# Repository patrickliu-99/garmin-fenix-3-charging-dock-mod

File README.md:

# garmin-fenix-3-charging-dock-mod
A quick PCB to add USB C charging to the Garmin Fenix 3 charging dock. Project made in KiCad 5.

# About
One of the charging clips I had for my Fenix 3 HR started failing - looked like the cable was damaged from overuse. I saw on Amazon that
replacements were available using USB micro B and figured I could do one better with USB C.

After a little fiddling about in KiCad, this project was made. More info to come on manufacturing and so on.

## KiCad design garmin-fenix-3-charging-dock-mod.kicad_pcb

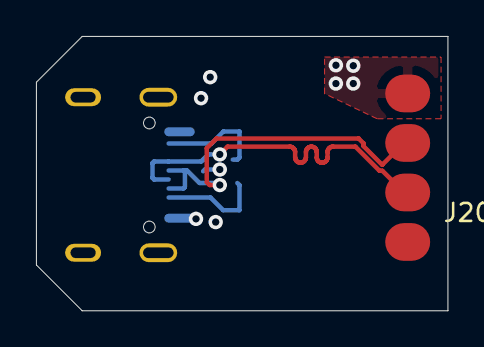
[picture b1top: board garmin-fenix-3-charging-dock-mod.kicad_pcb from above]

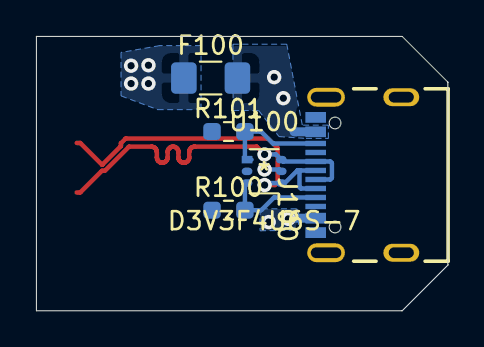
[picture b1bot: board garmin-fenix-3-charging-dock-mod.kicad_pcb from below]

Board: 4 copper layers, 22.9 x 15.2 mm, 6 parts (5 on the bottom side), 7 nets.

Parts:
F100: Polyfuse; Fuse_1206_3216Metric_Pad1.42x1.75mm_HandSolder
J100: USB4105_REVA; GCT_USB4105_REVA
J200: Garmin Fenix 3 Pogo Pins; Garmin Fenix 3 Charge Pins
R100, R101: 5.1k; R_0603_1608Metric_Pad0.98x0.95mm_HandSolder
U100: D3V3F4U6S-7

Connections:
/USBC_CC1: J100.A5, R100.1, U100.3
/USBC_CC2: J100.B5, R101.1, U100.1
/USB_D_N: J100.A7, J100.B7, J200.2, U100.4
/USB_D_P: J100.A6, J100.B6, J200.3, U100.6
/VBUS: F100.1, J200.1
/VBUS_RCPT: F100.2, J100.A4/B9, J100.B4/A9, U100.5
GND: J100.A1/B12, J100.B1/A12, J100.G1, J100.G2, J100.G3, J100.G4, J200.4, R100.2, R101.2, U100.2

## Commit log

2021-07-19 Initial commit of project
2021-07-19 Schematics complete
2021-07-19 Some layout complete, add TVS

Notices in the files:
parts and their libraries:
Copyright 2021 Accelerated Designs. All rights reserved.
